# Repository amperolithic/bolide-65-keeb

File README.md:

# Bolide65
Bolide65 is a 66 key, 65% keyboard with a rotary encoder and RGB backlighting under each key. It was built as a submission to Hack Club's [Forge](https://forge.hackclub.com/) YSWS program.

I was inspired to pursue this project after my sister's laptop's keyboard began acting up, preventing her from using the *t* and *u* key. She has to wait awhile before she can get a new laptop, so decided to make a keyboard for her in the meantime, using her design ideas (eg. incorporating lights) to make the keyboard and consulting her on its appearance and functionality throughout the process. Not only am I helping my sister, but this project really helped me gain more hardware experience (especially regarding routing and CAD).

## Features

- 66 cherry MX-compatible switch footprints in a custom 65% layout
- EC11 rotary encoder (push button enabled)
- RP2040 Zero microcontroller (USB-C) using QMK firmware
- 66 reverse mount SK6812MINI-E RGB LEDs on a single data chain
    - 74AHCT1G125 level shifter on the LED data line (3.3 V to 5 V) 
- 2-layer PCB with GND copper pours on both sides
- 4 PCB mounted stabilizers

## Layout

*The keymap layout (`Bolide65_Layout.json`) was made with [Keyboard Layout Editor NG](https://editor.keyboard-tools.xyz/).

A 6.25u screw-in stabilizers is needed for the Backspace key, while 2u screw-in stabilizers are needed for the Enter, Left Shift, and Space keys. Any 65% compatible keycap set will work with this project. The one listed in the BOM was chosen for its see-through effect and low cost. The blank space in the top-right corner of the keymap is on purpose, as it leaves room for the microcontroller and the encoder. The blank keys is meant to be a custom macro.

## PCB

This is the PCB (307x101mm) I made for Bolide65, made in KiCad 10.0. Most of the footprints came from the [Marbastlib](https://github.com/ebastler/marbastlib) library, the microcontroller footprint was sourced from [SnapMagic](https://www.snapeda.com/parts/RP2040-ZERO/Waveshare%20Electronics/view-part/), and anything else came from KiCad's default libraries. I used the kbplacer plugin to correctly arrage the switches according to my keymap. 

The microcontroller, LEDs, diodes, resistors, and capacitors are meant to be soldered to the back of the board, while everything else is soldered to the front. It is a 2 layer PCB with GND copper pours on both sides, and DRC passes with no errors!

**Schematic:**

The project is split across three sheets: the root sheet (microcontroller, level shifter, LED capacitors, stabilizers), the key matrix, and the LED chain.

**PCB:**

## Firmware 
The QMK firmware the keyboard microcontroller must be flashed with includes the matrix, encoder, and RGB matrix settings for the RP2040. Some notable firmware features are:
- Each function (F1, F2, etc) does not have its own button. Rather, each function can be accessed through the number row while holding down the `fn` key.
- The spare macro key switches through backlighting animations (normal press goes to next and shift goes back) and pressing it while on the `fn` setting changes the LED color.
- This keyboard uses the Grave Escape, so a plain press acts as the escape key, pressing shift inputs `~` and pressing it while on the `fn` setting inputs the backtick `.

## CAD

The PCB enclosure, designed in [Onshape](https://cad.onshape.com/documents/e20ea32dfc7030467aec0ff3/w/b7b45069ea496daed0bdf8db/e/1ffd2733c11c98bf9e533695?renderMode=0&uiState=6af77d7c11999bcd9a8952bf), utilizes a gummy-o-ring gasket keyboard mount style, hence, no screws are needed for this design. All one needs to do to assemble is solder the switches to the PCB, connect the switches to the top plate, add the o-ring (I recommended using the large blue GraveShift™ O-rings; the orange and green colors also work), and push it into the case. The case was designed to be made of Translucent 8001 Resin, so they keyboard can still *shine like a bolide*. Although any matierial of your choice can work. Similary, the final build will use a brass switch plate (to add weight to the keyboard) but a cheaper matierial such as FR4 or PLA will work). Although the rotary encoder has a custom knob, keycaps are meant to be outsourced. See through keycaps are recommneded fo this keyboard design.

Thanks to [Kael Ruland](https://github.com/anhthang/dsa-keycap), [GrabCAD](https://grabcad.com/library/cherry-mx-stabilizer-mx-1) and the [scottokeebs](https://github.com/joe-scotto/scottokeebs/tree/main/Extras/ScottoKicad/3dmodels) Github for some of the 3D models I used! 

| Item Name | Qty | Price (total) (USD) | Item Link | Notes |
| :--- | :---: | :---: | :--- | :--- |
| 330 Ω 0603 resistor [Uni-Royal 0603WAF3300T5E] | 100 | $0.26 | [LCSC](https://www.lcsc.com/product-detail/Chip-Resistor-Surface-Mount_UNI-ROYAL-Uniroyal-Elec-0603WAF3300T5E_C23138.html) | Must purchase 100 in order to source the 1 resistor needed. Purpose: To protect LED backlights and ensure stable signal transmission. |
| 0.1 µF Ceramic Capacitors [Samsung Electro-Mechanics CL10B104KB8NNNC] | 100 | $0.79 | [LCSC](https://www.lcsc.com/product-detail/C1591.html) | Must purchase 100 in order to source the 67 capacitors needed. Purpose: To smooth out power fluctuations and subsequently prevent LEDs from glitching or resetting. |
| 74AHCT1G125 Level Shifter [TI SN74AHCT1G125DBVR] | 5 | $0.50 | [LCSC](https://www.lcsc.com/product-detail/C7484.html) | Must purchase 5 in order to source the 1 level shifter needed. Purpose: To translate the low 3V3 voltage data from the RP2040 Zero to the higher level required by the LEDs. |
| Fast Switching Diode [Changzhou Starsea Elec 1N4148] | 100 | $1.34 | [LCSC](https://www.lcsc.com/product-detail/C85057.html) | Must purchase 100 in order to source the 67 diodes needed. Purpose: Used in matrix wiring to prevent ghosting from keyboard. |
| SK6812 MINI-E Addressable LEDs | 70 | $4.56 | [LCSC](https://www.lcsc.com/product-detail/Light-Emitting-Diodes-LED_OPSCO-Optoelectronics-SK6812MINI-E_C5149201.html) | Must purchase 70 in order to source the 66 LEDs needed. Purpose: To add programmable backlight to keyboard. |
| PCB | 1 | $19.00 | [Quote](https://github.com/ReuTheCoder/bolide-65-keeb/blob/main/assets/bolide-pcb_quote.png) | Uses default PCB settings on JLCPCB. |
| Womier Pudding Keycaps, Black PBT Shine Through (130 Keycap Set) | 1 | $12.61 | [Amazon.ca](https://www.amazon.ca/Womier-Pudding-Keyboard-Switches-Keyboard-Black/dp/B0D4DN5HK1?source=ps-sl-shoppingads-lpcontext&smid=AZ1RQDED92VC&th=1) | Keycap choice is not mandatory. Can choose other keycap set; see-through recommended. |
| PCB Mount Screw In Stabilizers (1x 6.25u, 4x 2u) | 1 | $4.72 | [Amazon.ca](https://www.amazon.ca/Mechanical-Keyboard-Stabilizers-Stabilizer-Backlight/dp/B0GS7HQJP6?source=ps-sl-shoppingads-lpcontext&th=1) | Stabilizer choice is not mandatory. Can choose other screw-in stabilizer set. |
| Glorious Fox Linear Mechanical Switches (110 pcs) | 1 | $23.09 | [Amazon.ca](https://www.amazon.ca/Glorious-Linear-Mechanical-Switches-Keyboards/dp/B0D7QW8SQ9/ref=pd_rhf_dp_s_pd_crcd_d_sccl_2_2/142-2623382-8190419?pd_rd_w=N9TW7&content-id=amzn1.sym.db0cabc9-3101-4abd-a708-693101cbc296&pf_rd_p=db0cabc9-3101-4abd-a708-693101cbc296&pf_rd_r=X0XF2N9P9SKDEEZ0JG4Q&pd_rd_wg=DsLHD&pd_rd_r=42983987-2f36-40de-b8c0-a3e2db3e17d2&pd_rd_i=B0D7QW8SQ9&th=1) | Switch choice is not mandatory. Can choose other MX-style switch. |
| Waveshare RP2040 Zero | 1 | $4.20 | [RobotShop](https://ca.robotshop.com/products/rp2040-zero-pico-like-mcu-board-based-on-rp2040-mini-version-w-o-header) | Ensure you have pin headers. |
| EC11 Rotary Encoder | 1 | $2.22 | [LCSC](https://www.lcsc.com/product-detail/C202365.html) | CAD files have custom knob. |
| Rotary Encoder Knob | 1 | $0.32 | [Quote](https://github.com/ReuTheCoder/bolide-65-keeb/blob/main/assets/readme/bolide-CAD_quote.png) | Uses 9600 Resin. |
| GraveShift™ Large Blue O-ring | 1 | $6.10 | [Mech.land](https://mech.land/products/graveshift-o-rings?variant=43233476739299) | Green and Orange also recommended. |
| Case | 1 | $39.29 | [Quote](https://github.com/amperolithic/bolide-65-keeb/blob/main/assets/readme/bolide-CAD_case.png) | Uses 9600 Resin; did not use 8001 Resin as it is over $100. |
| Switch Plate | 1 | $26.89 | [Quote](https://github.com/amperolithic/bolide-65-keeb/blob/main/assets/readme/bolide-switch_plate.png) | Uses Brass; can use cheaper material. |
| **Total Price (USD):** | | **$145.89** | | |

## Additonal Notes

This was my second ever PCB project and I am quite satisfied with what I could get done in a week! Below is an explanation of some technical choices I made for my PCB schematics:
- No hotswap; this keyboard is meant to have all its components hand soldered to it. It's cheaper, and I wanted to get more soldering experience through this project.
- The encoder's push button is wired through the matrix (9 columns by 8 rows) so it can be used when pushed (function not decided yet) while its rotation pins go straight to the microcontroller GPIO.
- To protect my LEDs and ensure stable signal transmission, its data chain passes through the level shifter (U2) and a 330 Ω series resistor (R1) before LED1, and every LED has its own 0.1 µF decoupling capacitor (C2-C67), with C1 for the shifter. I did not add a bulk capacitor, so brightness should be capped in firmware to stay within USB power limits.
- I know my routing is horrendous, but it gets the job done. I hope to imprve my routing capabilities as I continue to make more PCBs.

| Keycap | Size |
|---|---|
| Backspace | 2u |
| Tab, Backslash | 1.5u |
| Caps Lock, Right Shift | 1.75u |
| Enter, Left Shift | 2.25u |
| Ctrl, Menu, Left Alt | 1.25u |
| Space | 6.25u |
| All remaining keys | 1u |

Many thanks to the creators of Marbastlib and kbplacer for making my life easier during the design process. Also, I would like to say **thank you so much** to the organizers of [Forge](https://forge.hackclub.com/) and those at the [HackClub](https://hackclub.com/) hq for this wonderful hardware exploration opportunity!

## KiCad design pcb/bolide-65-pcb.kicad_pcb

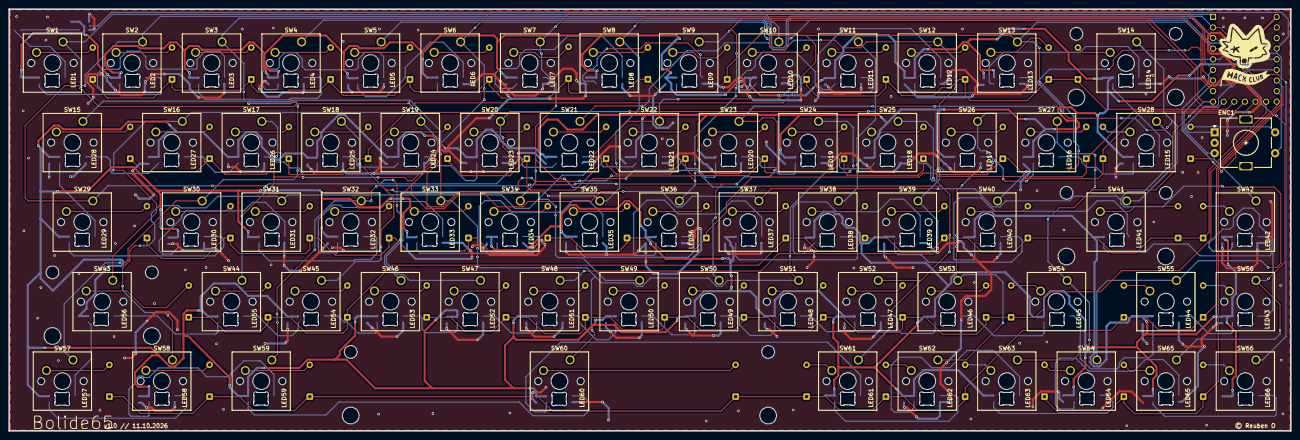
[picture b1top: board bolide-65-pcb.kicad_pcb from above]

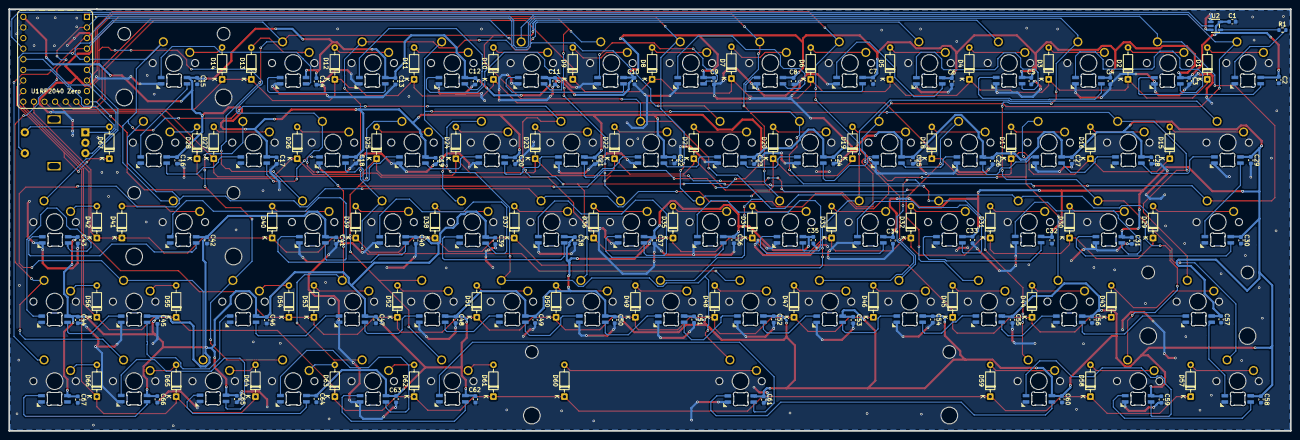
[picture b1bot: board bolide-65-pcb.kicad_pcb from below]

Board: 2 copper layers, 307.0 x 101.0 mm, 270 parts (137 on the bottom side), 156 nets.

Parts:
C1, C2, C3, C4, C5, C6, C7, C8, C9, C10, C11, C12, C13, C14, C15, C16, C17, C18, C19, C20, C21, C22, C23, C24, C25, C26, C27, C28, C29, C30, C31, C32, C33, C34, C35, C36, C37, C38, C39, C40, C41, C42, C43, C44, C45, C46, C47, C48, C49, C50, C51, C52, C53, C54, C55, C56, C57, C58, C59, C60, C61, C62, C63, C64, C65, C66, C67: 100nF; C_0603_1608Metric
D1, D2, D3, D4, D5, D6, D7, D8, D9, D10, D11, D12, D13, D14, D15, D16, D17, D18, D19, D20, D21, D22, D23, D24, D25, D26, D27, D28, D29, D30, D31, D32, D33, D34, D35, D36, D37, D38, D39, D40, D41, D42, D43, D44, D45, D46, D47, D48, D49, D50, D51, D52, D53, D54, D55, D56, D57, D58, D59, D60, D61, D62, D63, D64, D65, D66, D67: 1N4148; D_DO-35_SOD27_P7.62mm_Horizontal
ENC1: RotaryEncoder_Switch; RotaryEncoder_Alps_EC11E-Switch_Vertical_H20mm
LED1, LED2, LED3, LED4, LED5, LED6, LED7, LED8, LED9, LED10, LED11, LED12, LED13, LED14, LED15, LED16, LED17, LED18, LED19, LED20, LED21, LED22, LED23, LED24, LED25, LED26, LED27, LED28, LED29, LED30, LED31, LED32, LED33, LED34, LED35, LED36, LED37, LED38, LED39, LED40, LED41, LED42, LED43, LED44, LED45, LED46, LED47, LED48, LED49, LED50, LED51, LED52, LED53, LED54, LED55, LED56, LED57, LED58, LED59, LED60, LED61, LED62, LED63, LED64, LED65, LED66: SK6812MINI-E; SK6812MINI-E_fixed
R1: 330; R_0603_1608Metric
SW1: Backtick; SW_Cherry_MX_1.00u_PCB
SW2: 1; SW_Cherry_MX_1.00u_PCB
SW3: 2; SW_Cherry_MX_1.00u_PCB
SW4: 3; SW_Cherry_MX_1.00u_PCB
SW5: 4; SW_Cherry_MX_1.00u_PCB
SW6: 5; SW_Cherry_MX_1.00u_PCB
SW7: 6; SW_Cherry_MX_1.00u_PCB
SW8: 7; SW_Cherry_MX_1.00u_PCB
SW9: 8; SW_Cherry_MX_1.00u_PCB
SW10: 9; SW_Cherry_MX_1.00u_PCB
SW11: 0; SW_Cherry_MX_1.00u_PCB
SW12: Minus; SW_Cherry_MX_1.00u_PCB
SW13: Equals; SW_Cherry_MX_1.00u_PCB
SW14: Backspace; SW_Cherry_MX_2.00u_PCB
SW15: Tab; SW_Cherry_MX_1.50u_PCB
SW16: Q; SW_Cherry_MX_1.00u_PCB
SW17: W; SW_Cherry_MX_1.00u_PCB
SW18: E; SW_Cherry_MX_1.00u_PCB
SW19: R; SW_Cherry_MX_1.00u_PCB
SW20: T; SW_Cherry_MX_1.00u_PCB
SW21: Y; SW_Cherry_MX_1.00u_PCB
SW22: U; SW_Cherry_MX_1.00u_PCB
SW23: I; SW_Cherry_MX_1.00u_PCB
SW24: O; SW_Cherry_MX_1.00u_PCB
SW25: P; SW_Cherry_MX_1.00u_PCB
SW26: LBracket; SW_Cherry_MX_1.00u_PCB
SW27: RBracket; SW_Cherry_MX_1.00u_PCB
SW28: Backslash; SW_Cherry_MX_1.50u_PCB
SW29: CapsLock; SW_Cherry_MX_1.75u_PCB
SW30: A; SW_Cherry_MX_1.00u_PCB
SW31: S; SW_Cherry_MX_1.00u_PCB
SW32: D; SW_Cherry_MX_1.00u_PCB
SW33: F; SW_Cherry_MX_1.00u_PCB
SW34: G; SW_Cherry_MX_1.00u_PCB
SW35: H; SW_Cherry_MX_1.00u_PCB
SW36: J; SW_Cherry_MX_1.00u_PCB
SW37: K; SW_Cherry_MX_1.00u_PCB
SW38: L; SW_Cherry_MX_1.00u_PCB
SW39: Semicolon; SW_Cherry_MX_1.00u_PCB
SW40: Quote; SW_Cherry_MX_1.00u_PCB
SW41: Enter; SW_Cherry_MX_2.25u_PCB
SW42: PgUp; SW_Cherry_MX_1.00u_PCB
SW43: LShift; SW_Cherry_MX_2.25u_PCB
SW44: Z; SW_Cherry_MX_1.00u_PCB
SW45: X; SW_Cherry_MX_1.00u_PCB
SW46: C; SW_Cherry_MX_1.00u_PCB
SW47: V; SW_Cherry_MX_1.00u_PCB
SW48: B; SW_Cherry_MX_1.00u_PCB
SW49: N; SW_Cherry_MX_1.00u_PCB
SW50: M; SW_Cherry_MX_1.00u_PCB
SW51: Comma; SW_Cherry_MX_1.00u_PCB
SW52: Period; SW_Cherry_MX_1.00u_PCB
SW53: Slash; SW_Cherry_MX_1.00u_PCB
SW54: RShift; SW_Cherry_MX_1.75u_PCB
SW55: Up; SW_Cherry_MX_1.00u_PCB
SW56: PgDown; SW_Cherry_MX_1.00u_PCB
SW57: LCtrl; SW_Cherry_MX_1.25u_PCB
SW58: Menu; SW_Cherry_MX_1.25u_PCB
SW59: LAlt; SW_Cherry_MX_1.25u_PCB
SW60: Space; SW_Cherry_MX_6.25u_PCB
SW61: RAlt; SW_Cherry_MX_1.00u_PCB
SW62: Fn; SW_Cherry_MX_1.00u_PCB
SW63: Blank; SW_Cherry_MX_1.00u_PCB
SW64: Left; SW_Cherry_MX_1.00u_PCB
SW65: Down; SW_Cherry_MX_1.00u_PCB
SW66: Right; SW_Cherry_MX_1.00u_PCB
U1: RP2040-ZERO; MODULE_RP2040-ZERO
U2: 74AHCT1G125; SOT-23-5

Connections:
+5V: C1.1, C2.1, C3.1, C4.1, C5.1, C6.1, C7.1, C8.1, C9.1, C10.1, C11.1, C12.1, C13.1, C14.1, C15.1, C16.1, C17.1, C18.1, C19.1, C20.1, C21.1, C22.1, C23.1, C24.1, C25.1, C26.1, C27.1, C28.1, C29.1, C30.1, C31.1, C32.1, C33.1, C34.1, C35.1, C36.1, C37.1, C38.1, C39.1, C40.1, C41.1, C42.1, C43.1, C44.1, C45.1, C46.1, C47.1, C48.1, C49.1, C50.1, C51.1, C52.1, C53.1, C54.1, C55.1, C56.1, C57.1, C58.1, C59.1, C60.1, C61.1, C62.1, C63.1, C64.1, C65.1, C66.1, C67.1, LED1.1 (VDD), LED2.1 (VDD), LED3.1 (VDD), LED4.1 (VDD), LED5.1 (VDD), LED6.1 (VDD), LED7.1 (VDD), LED8.1 (VDD), LED9.1 (VDD), LED10.1 (VDD), LED11.1 (VDD), LED12.1 (VDD), LED13.1 (VDD), LED14.1 (VDD), LED15.1 (VDD), LED16.1 (VDD), LED17.1 (VDD), LED18.1 (VDD), LED19.1 (VDD), LED20.1 (VDD), LED21.1 (VDD), LED22.1 (VDD), LED23.1 (VDD), LED24.1 (VDD), LED25.1 (VDD), LED26.1 (VDD), LED27.1 (VDD), LED28.1 (VDD), LED29.1 (VDD), LED30.1 (VDD), LED31.1 (VDD), LED32.1 (VDD), LED33.1 (VDD), LED34.1 (VDD), LED35.1 (VDD), LED36.1 (VDD), LED37.1 (VDD), LED38.1 (VDD), LED39.1 (VDD), LED40.1 (VDD), LED41.1 (VDD), LED42.1 (VDD), LED43.1 (VDD), LED44.1 (VDD), LED45.1 (VDD), LED46.1 (VDD), LED47.1 (VDD), LED48.1 (VDD), LED49.1 (VDD), LED50.1 (VDD), LED51.1 (VDD), LED52.1 (VDD), LED53.1 (VDD), LED54.1 (VDD), LED55.1 (VDD), LED56.1 (VDD), LED57.1 (VDD), LED58.1 (VDD), LED59.1 (VDD), LED60.1 (VDD), LED61.1 (VDD), LED62.1 (VDD), LED63.1 (VDD), LED64.1 (VDD), LED65.1 (VDD), LED66.1 (VDD), U1.23 (5V), U2.5 (VCC)
COL0: SW1.1, SW10.1, SW19.1, SW28.1, SW37.1, SW46.1, SW55.1, SW64.1, U1.1 (GP0)
COL1: SW2.1, SW11.1, SW20.1, SW29.1, SW38.1, SW47.1, SW56.1, SW65.1, U1.2 (GP1)
COL2: SW3.1, SW12.1, SW21.1, SW30.1, SW39.1, SW48.1, SW57.1, SW66.1, U1.3 (GP2)
COL3: ENC1.S1, SW4.1, SW13.1, SW22.1, SW31.1, SW40.1, SW49.1, SW58.1, U1.4 (GP3)
COL4: SW5.1, SW14.1, SW23.1, SW32.1, SW41.1, SW50.1, SW59.1, U1.5 (GP4)
COL5: SW6.1, SW15.1, SW24.1, SW33.1, SW42.1, SW51.1, SW60.1, U1.6 (GP5)
COL6: SW7.1, SW16.1, SW25.1, SW34.1, SW43.1, SW52.1, SW61.1, U1.7 (GP6)
COL7: SW8.1, SW17.1, SW26.1, SW35.1, SW44.1, SW53.1, SW62.1, U1.8 (GP7)
COL8: SW9.1, SW18.1, SW27.1, SW36.1, SW45.1, SW54.1, SW63.1, U1.9 (GP8)
ENC_A: ENC1.A, U1.18 (GP27)
ENC_B: ENC1.B, U1.19 (GP28)
GND: C1.2, C2.2, C3.2, C4.2, C5.2, C6.2, C7.2, C8.2, C9.2, C10.2, C11.2, C12.2, C13.2, C14.2, C15.2, C16.2, C17.2, C18.2, C19.2, C20.2, C21.2, C22.2, C23.2, C24.2, C25.2, C26.2, C27.2, C28.2, C29.2, C30.2, C31.2, C32.2, C33.2, C34.2, C35.2, C36.2, C37.2, C38.2, C39.2, C40.2, C41.2, C42.2, C43.2, C44.2, C45.2, C46.2, C47.2, C48.2, C49.2, C50.2, C51.2, C52.2, C53.2, C54.2, C55.2, C56.2, C57.2, C58.2, C59.2, C60.2, C61.2, C62.2, C63.2, C64.2, C65.2, C66.2, C67.2, ENC1.C, LED1.3 (VSS), LED2.3 (VSS), LED3.3 (VSS), LED4.3 (VSS), LED5.3 (VSS), LED6.3 (VSS), LED7.3 (VSS), LED8.3 (VSS), LED9.3 (VSS), LED10.3 (VSS), LED11.3 (VSS), LED12.3 (VSS), LED13.3 (VSS), LED14.3 (VSS), LED15.3 (VSS), LED16.3 (VSS), LED17.3 (VSS), LED18.3 (VSS), LED19.3 (VSS), LED20.3 (VSS), LED21.3 (VSS), LED22.3 (VSS), LED23.3 (VSS), LED24.3 (VSS), LED25.3 (VSS), LED26.3 (VSS), LED27.3 (VSS), LED28.3 (VSS), LED29.3 (VSS), LED30.3 (VSS), LED31.3 (VSS), LED32.3 (VSS), LED33.3 (VSS), LED34.3 (VSS), LED35.3 (VSS), LED36.3 (VSS), LED37.3 (VSS), LED38.3 (VSS), LED39.3 (VSS), LED40.3 (VSS), LED41.3 (VSS), LED42.3 (VSS), LED43.3 (VSS), LED44.3 (VSS), LED45.3 (VSS), LED46.3 (VSS), LED47.3 (VSS), LED48.3 (VSS), LED49.3 (VSS), LED50.3 (VSS), LED51.3 (VSS), LED52.3 (VSS), LED53.3 (VSS), LED54.3 (VSS), LED55.3 (VSS), LED56.3 (VSS), LED57.3 (VSS), LED58.3 (VSS), LED59.3 (VSS), LED60.3 (VSS), LED61.3 (VSS), LED62.3 (VSS), LED63.3 (VSS), LED64.3 (VSS), LED65.3 (VSS), LED66.3 (VSS), U1.22 (GND), U2.1, U2.3 (GND)
LED_DATA: U1.20 (GP29), U2.2
unnamed: D1.2 (A), SW1.2
unnamed: D2.2 (A), SW2.2
unnamed: D3.2 (A), SW3.2
unnamed: D4.2 (A), SW4.2
unnamed: D5.2 (A), SW5.2
unnamed: D6.2 (A), SW6.2
unnamed: D7.2 (A), SW7.2
unnamed: D8.2 (A), SW8.2
unnamed: D9.2 (A), SW9.2
unnamed: D10.2 (A), SW10.2
unnamed: D11.2 (A), SW11.2
unnamed: D12.2 (A), SW12.2
unnamed: D13.2 (A), SW13.2
unnamed: D14.2 (A), SW14.2
unnamed: D15.2 (A), SW15.2
unnamed: D16.2 (A), SW16.2
unnamed: D17.2 (A), SW17.2
unnamed: D18.2 (A), SW18.2
unnamed: D19.2 (A), SW19.2
unnamed: D20.2 (A), SW20.2
unnamed: D21.2 (A), SW21.2
unnamed: D22.2 (A), SW22.2
unnamed: D23.2 (A), SW23.2
unnamed: D24.2 (A), SW24.2
unnamed: D25.2 (A), SW25.2
unnamed: D26.2 (A), SW26.2
unnamed: D27.2 (A), SW27.2
unnamed: D28.2 (A), SW28.2
unnamed: D29.2 (A), SW29.2
unnamed: D30.2 (A), SW30.2
unnamed: D31.2 (A), SW31.2
unnamed: D32.2 (A), SW32.2
unnamed: D33.2 (A), SW33.2
unnamed: D34.2 (A), SW34.2
unnamed: D35.2 (A), SW35.2
unnamed: D36.2 (A), SW36.2
unnamed: D37.2 (A), SW37.2
unnamed: D38.2 (A), SW38.2
unnamed: D39.2 (A), SW39.2
unnamed: D40.2 (A), SW40.2
unnamed: D41.2 (A), SW41.2
unnamed: D42.2 (A), SW42.2
unnamed: D43.2 (A), SW43.2
unnamed: D44.2 (A), SW44.2
unnamed: D45.2 (A), SW45.2
unnamed: D46.2 (A), SW46.2
unnamed: D47.2 (A), SW47.2
unnamed: D48.2 (A), SW48.2
unnamed: D49.2 (A), SW49.2
unnamed: D50.2 (A), SW50.2
unnamed: D51.2 (A), SW51.2
unnamed: D52.2 (A), SW52.2
unnamed: D53.2 (A), SW53.2
unnamed: D54.2 (A), SW54.2
unnamed: D55.2 (A), SW55.2
unnamed: D56.2 (A), SW56.2
unnamed: D57.2 (A), SW57.2
unnamed: D58.2 (A), SW58.2
unnamed: D59.2 (A), SW59.2
unnamed: D60.2 (A), SW60.2
unnamed: D61.2 (A), SW61.2
unnamed: D62.2 (A), SW62.2
unnamed: D63.2 (A), SW63.2
unnamed: D64.2 (A), SW64.2
unnamed: D65.2 (A), SW65.2
unnamed: D66.2 (A), SW66.2
unnamed: D67.2 (A), ENC1.S2
unnamed: LED1.4 (DIN), R1.2
unnamed: LED1.2 (DOUT), LED2.4 (DIN)
unnamed: LED2.2 (DOUT), LED3.4 (DIN)
unnamed: LED3.2 (DOUT), LED4.4 (DIN)
unnamed: LED4.2 (DOUT), LED5.4 (DIN)
unnamed: LED5.2 (DOUT), LED6.4 (DIN)
unnamed: LED6.2 (DOUT), LED7.4 (DIN)
unnamed: LED7.2 (DOUT), LED8.4 (DIN)
unnamed: LED8.2 (DOUT), LED9.4 (DIN)
unnamed: LED9.2 (DOUT), LED10.4 (DIN)
unnamed: LED10.2 (DOUT), LED11.4 (DIN)
unnamed: LED11.2 (DOUT), LED12.4 (DIN)
unnamed: LED12.2 (DOUT), LED13.4 (DIN)
unnamed: LED13.2 (DOUT), LED14.4 (DIN)
unnamed: LED14.2 (DOUT), LED15.4 (DIN)
unnamed: LED15.2 (DOUT), LED16.4 (DIN)
unnamed: LED16.2 (DOUT), LED17.4 (DIN)
unnamed: LED17.2 (DOUT), LED18.4 (DIN)
unnamed: LED18.2 (DOUT), LED19.4 (DIN)
unnamed: LED19.2 (DOUT), LED20.4 (DIN)
unnamed: LED20.2 (DOUT), LED21.4 (DIN)
unnamed: LED21.2 (DOUT), LED22.4 (DIN)
unnamed: LED22.2 (DOUT), LED23.4 (DIN)
unnamed: LED23.2 (DOUT), LED24.4 (DIN)
unnamed: LED24.2 (DOUT), LED25.4 (DIN)
unnamed: LED25.2 (DOUT), LED26.4 (DIN)
unnamed: LED26.2 (DOUT), LED27.4 (DIN)
unnamed: LED27.2 (DOUT), LED28.4 (DIN)
unnamed: LED28.2 (DOUT), LED29.4 (DIN)
unnamed: LED29.2 (DOUT), LED30.4 (DIN)
unnamed: LED30.2 (DOUT), LED31.4 (DIN)
unnamed: LED31.2 (DOUT), LED32.4 (DIN)
unnamed: LED32.2 (DOUT), LED33.4 (DIN)
unnamed: LED33.2 (DOUT), LED34.4 (DIN)
unnamed: LED34.2 (DOUT), LED35.4 (DIN)
unnamed: LED35.2 (DOUT), LED36.4 (DIN)
unnamed: LED36.2 (DOUT), LED37.4 (DIN)
unnamed: LED37.2 (DOUT), LED38.4 (DIN)
unnamed: LED38.2 (DOUT), LED39.4 (DIN)
unnamed: LED39.2 (DOUT), LED40.4 (DIN)
unnamed: LED40.2 (DOUT), LED41.4 (DIN)
unnamed: LED41.2 (DOUT), LED42.4 (DIN)
unnamed: LED42.2 (DOUT), LED43.4 (DIN)
unnamed: LED43.2 (DOUT), LED44.4 (DIN)
unnamed: LED44.2 (DOUT), LED45.4 (DIN)
unnamed: LED45.2 (DOUT), LED46.4 (DIN)
unnamed: LED46.2 (DOUT), LED47.4 (DIN)
unnamed: LED47.2 (DOUT), LED48.4 (DIN)
unnamed: LED48.2 (DOUT), LED49.4 (DIN)
unnamed: LED49.2 (DOUT), LED50.4 (DIN)
unnamed: LED50.2 (DOUT), LED51.4 (DIN)
unnamed: LED51.2 (DOUT), LED52.4 (DIN)
unnamed: LED52.2 (DOUT), LED53.4 (DIN)
unnamed: LED53.2 (DOUT), LED54.4 (DIN)
unnamed: LED54.2 (DOUT), LED55.4 (DIN)
unnamed: LED55.2 (DOUT), LED56.4 (DIN)
unnamed: LED56.2 (DOUT), LED57.4 (DIN)
unnamed: LED57.2 (DOUT), LED58.4 (DIN)
unnamed: LED58.2 (DOUT), LED59.4 (DIN)
unnamed: LED59.2 (DOUT), LED60.4 (DIN)
unnamed: LED60.2 (DOUT), LED61.4 (DIN)
unnamed: LED61.2 (DOUT), LED62.4 (DIN)
unnamed: LED62.2 (DOUT), LED63.4 (DIN)
unnamed: LED63.2 (DOUT), LED64.4 (DIN)
unnamed: LED64.2 (DOUT), LED65.4 (DIN)
unnamed: LED65.2 (DOUT), LED66.4 (DIN)
ROW0: D1.1 (K), D2.1 (K), D3.1 (K), D4.1 (K), D5.1 (K), D6.1 (K), D7.1 (K), D8.1 (K), D9.1 (K), U1.10 (GP9)
ROW1: D10.1 (K), D11.1 (K), D12.1 (K), D13.1 (K), D14.1 (K), D15.1 (K), D16.1 (K), D17.1 (K), D18.1 (K), U1.11 (GP10)
ROW2: D19.1 (K), D20.1 (K), D21.1 (K), D22.1 (K), D23.1 (K), D24.1 (K), D25.1 (K), D26.1 (K), D27.1 (K), U1.12 (GP11)
ROW3: D28.1 (K), D29.1 (K), D30.1 (K), D31.1 (K), D32.1 (K), D33.1 (K), D34.1 (K), D35.1 (K), D36.1 (K), U1.13 (GP12)
ROW4: D37.1 (K), D38.1 (K), D39.1 (K), D40.1 (K), D41.1 (K), D42.1 (K), D43.1 (K), D44.1 (K), D45.1 (K), U1.14 (GP13)
ROW5: D46.1 (K), D47.1 (K), D48.1 (K), D49.1 (K), D50.1 (K), D51.1 (K), D52.1 (K), D53.1 (K), D54.1 (K), U1.15 (GP14)
ROW6: D55.1 (K), D56.1 (K), D57.1 (K), D58.1 (K), D59.1 (K), D60.1 (K), D61.1 (K), D62.1 (K), D63.1 (K), U1.16 (GP15)
ROW7: D64.1 (K), D65.1 (K), D66.1 (K), D67.1 (K), U1.17 (GP26)
SHIFTER: R1.1, U2.4

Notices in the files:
pcb/bolide-65-pcb.kicad_pcb:
© Reuben O
